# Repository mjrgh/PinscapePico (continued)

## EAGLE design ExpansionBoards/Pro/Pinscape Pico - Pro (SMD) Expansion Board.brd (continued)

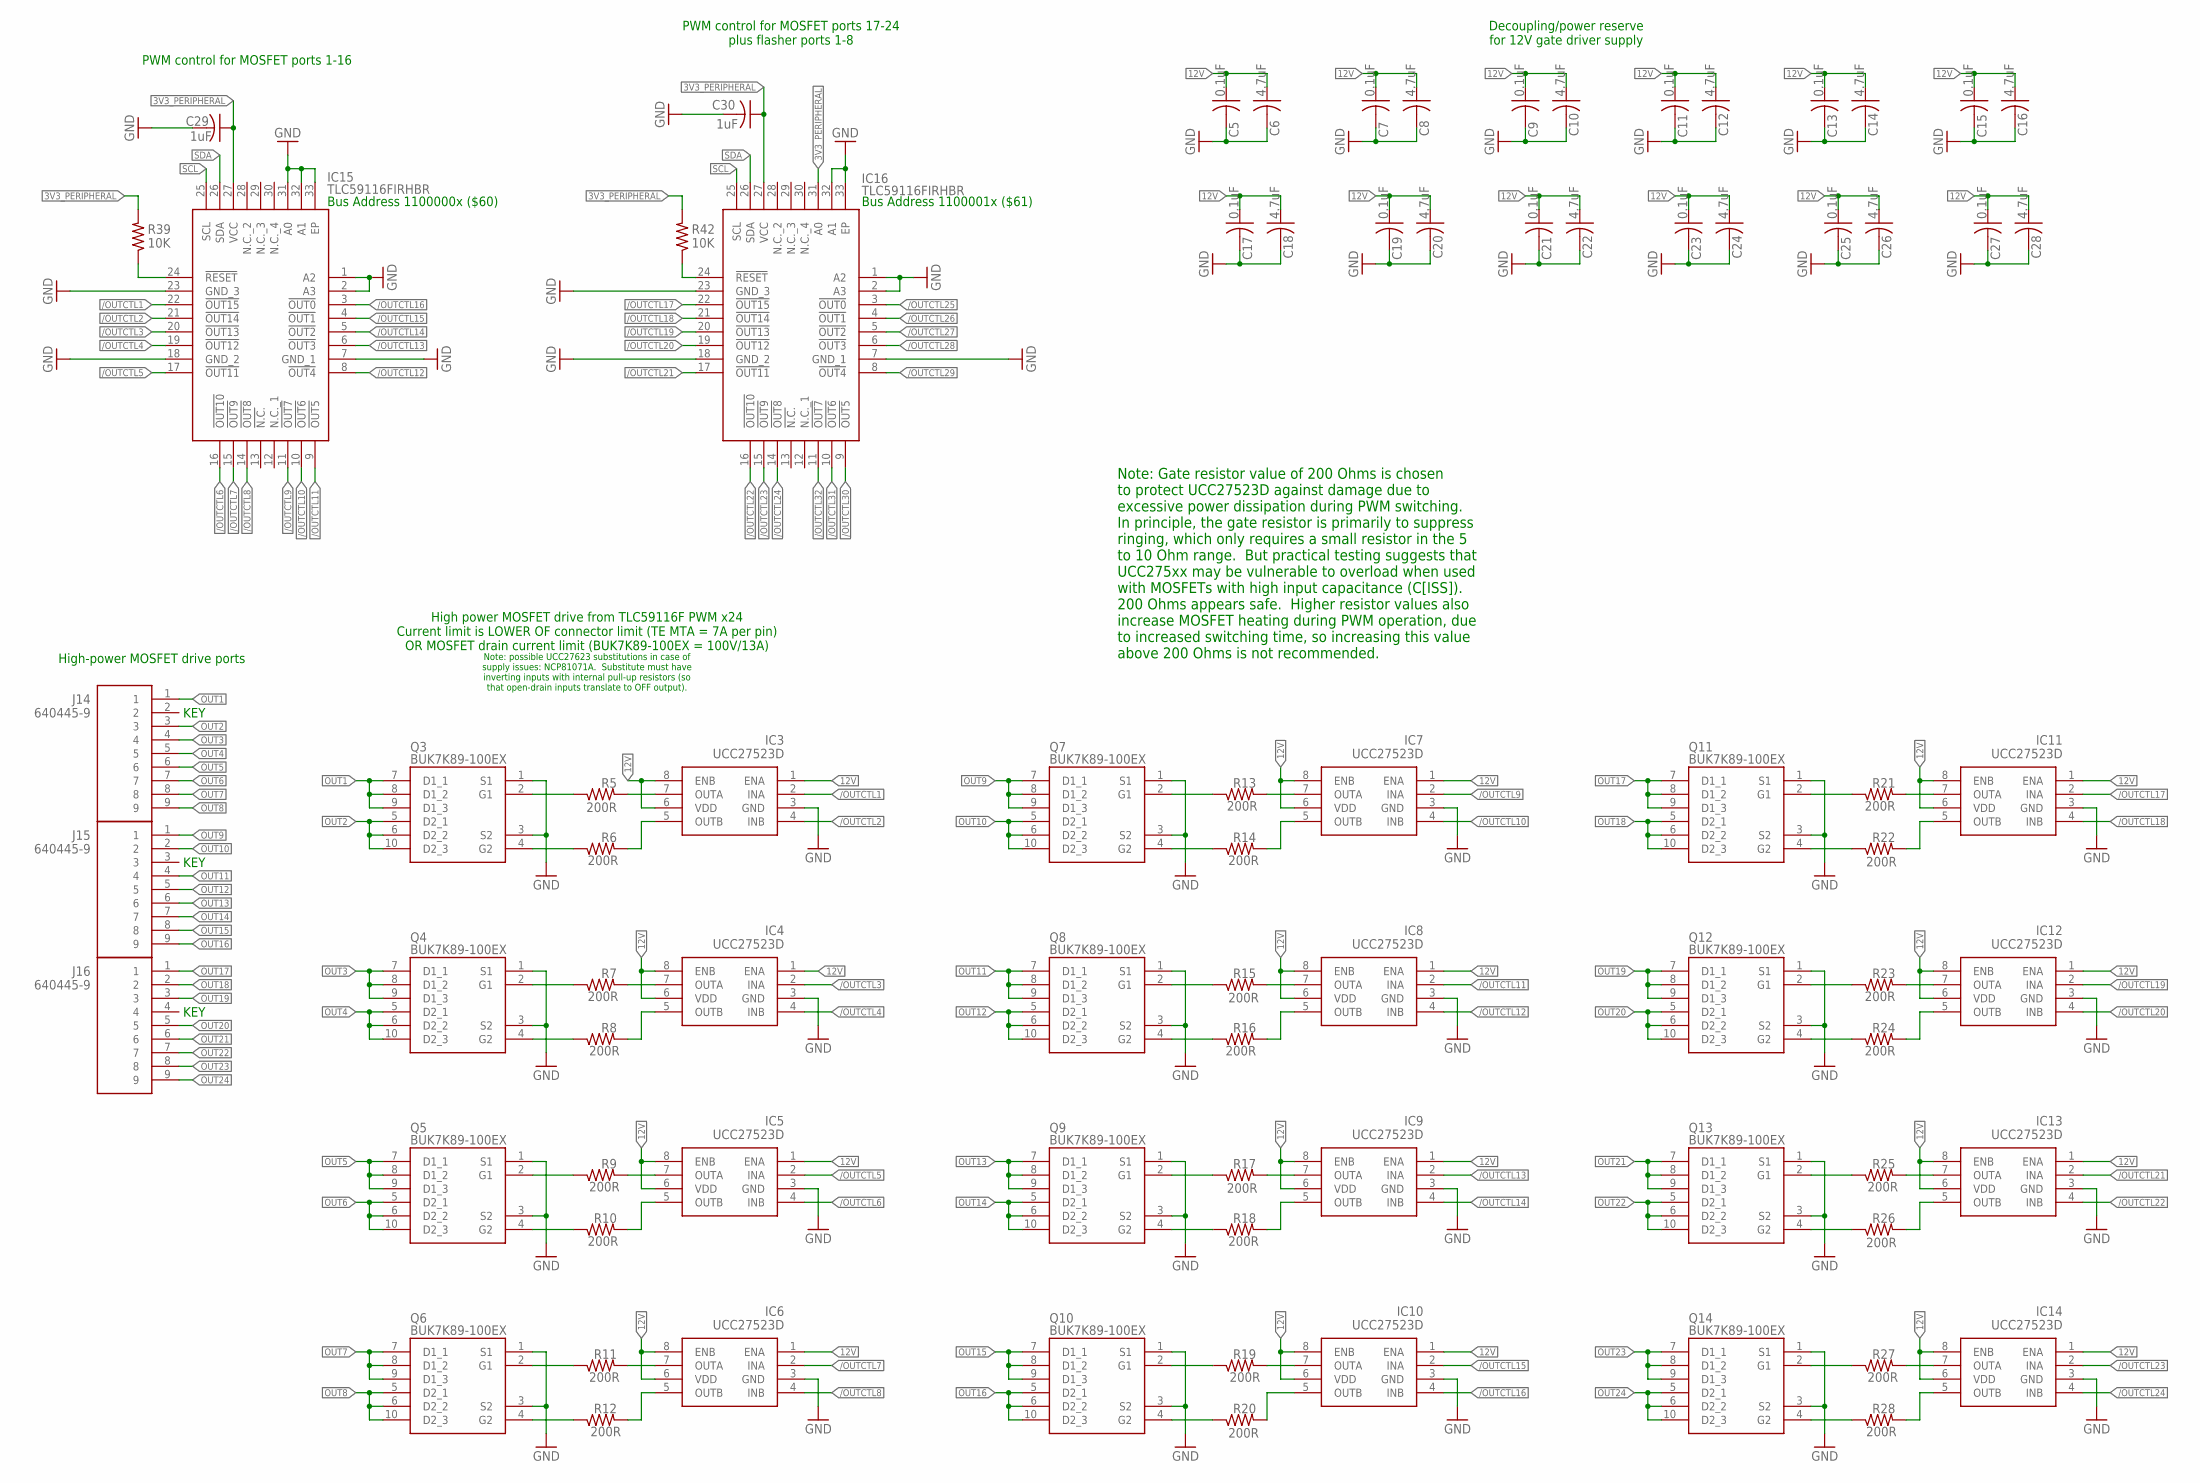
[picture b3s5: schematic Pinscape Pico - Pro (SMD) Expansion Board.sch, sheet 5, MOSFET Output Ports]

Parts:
C5, C7, C9, C11, C13, C15, C17, C19, C21, C23, C25, C27: 0.1uF; C0402
C6, C8, C10, C12, C14, C16, C18, C20, C22, C24, C26, C28: 4.7uF; C1206
C29, C30: 1uF; C0402
IC3, IC4, IC5, IC6, IC7, IC8, IC9, IC10, IC11, IC12, IC13, IC14: UCC27523D; SOIC127P600X175-8N
IC15, IC16: TLC59116FIRHBR; QFN50P500X500X100-33N
J14, J15, J16: 640445-9; SHDR9W117P0X396_1X9_3566X762X1
Q3, Q4, Q5, Q6, Q7, Q8, Q9, Q10, Q11, Q12, Q13, Q14: BUK7K89-100EX; BUK7K89100EX
R5, R6, R7, R8, R9, R10, R11, R12, R13, R14, R15, R16, R17, R18, R19, R20, R21, R22, R23, R24, R25, R26, R27, R28: 200R; R0603
R39, R42: 10K; R0402

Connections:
3V3_PERIPHERAL: C29.1, C30.1, IC15.27 (VCC), IC16.27 (VCC), IC16.31 (A0), R39.2, R42.2; also elsewhere on the board
12V: C5.1, C6.1, C7.1, C8.1, C9.1, C10.1, C11.1, C12.1, C13.1, C14.1, C15.1, C16.1, C17.1, C18.1, C19.1, C20.1, C21.1, C22.1, C23.1, C24.1, C25.1, C26.1, C27.1, C28.1, IC3.1 (ENA), IC3.6 (VDD), IC3.8 (ENB), IC4.1 (ENA), IC4.6 (VDD), IC4.8 (ENB), IC5.1 (ENA), IC5.6 (VDD), IC5.8 (ENB), IC6.1 (ENA), IC6.6 (VDD), IC6.8 (ENB), IC7.1 (ENA), IC7.6 (VDD), IC7.8 (ENB), IC8.1 (ENA), IC8.6 (VDD), IC8.8 (ENB), IC9.1 (ENA), IC9.6 (VDD), IC9.8 (ENB), IC10.1 (ENA), IC10.6 (VDD), IC10.8 (ENB), IC11.1 (ENA), IC11.6 (VDD), IC11.8 (ENB), IC12.1 (ENA), IC12.6 (VDD), IC12.8 (ENB), IC13.1 (ENA), IC13.6 (VDD), IC13.8 (ENB), IC14.1 (ENA), IC14.6 (VDD), IC14.8 (ENB); also elsewhere on the board
/OUTCTL1: IC3.2 (INA), IC15.22 (!OUT15)
/OUTCTL2: IC3.4 (INB), IC15.21 (!OUT14)
/OUTCTL3: IC4.2 (INA), IC15.20 (!OUT13)
/OUTCTL4: IC4.4 (INB), IC15.19 (!OUT12)
/OUTCTL5: IC5.2 (INA), IC15.17 (!OUT11)
/OUTCTL6: IC5.4 (INB), IC15.16 (!OUT10)
/OUTCTL7: IC6.2 (INA), IC15.15 (!OUT9)
/OUTCTL8: IC6.4 (INB), IC15.14 (!OUT8)
/OUTCTL9: IC7.2 (INA), IC15.11 (!OUT7)
/OUTCTL10: IC7.4 (INB), IC15.10 (!OUT6)
/OUTCTL11: IC8.2 (INA), IC15.9 (!OUT5)
/OUTCTL12: IC8.4 (INB), IC15.8 (!OUT4)
/OUTCTL13: IC9.2 (INA), IC15.6 (!OUT3)
/OUTCTL14: IC9.4 (INB), IC15.5 (!OUT2)
/OUTCTL15: IC10.2 (INA), IC15.4 (!OUT1)
/OUTCTL16: IC10.4 (INB), IC15.3 (!OUT0)
/OUTCTL17: IC11.2 (INA), IC16.22 (!OUT15)
/OUTCTL18: IC11.4 (INB), IC16.21 (!OUT14)
/OUTCTL19: IC12.2 (INA), IC16.20 (!OUT13)
/OUTCTL20: IC12.4 (INB), IC16.19 (!OUT12)
/OUTCTL21: IC13.2 (INA), IC16.17 (!OUT11)
/OUTCTL22: IC13.4 (INB), IC16.16 (!OUT10)
/OUTCTL23: IC14.2 (INA), IC16.15 (!OUT9)
/OUTCTL24: IC14.4 (INB), IC16.14 (!OUT8)
/OUTCTL25: IC16.3 (!OUT0); also elsewhere on the board
/OUTCTL26: IC16.4 (!OUT1); also elsewhere on the board
/OUTCTL27: IC16.5 (!OUT2); also elsewhere on the board
/OUTCTL28: IC16.6 (!OUT3); also elsewhere on the board
/OUTCTL29: IC16.8 (!OUT4); also elsewhere on the board
/OUTCTL30: IC16.9 (!OUT5); also elsewhere on the board
/OUTCTL31: IC16.10 (!OUT6); also elsewhere on the board
/OUTCTL32: IC16.11 (!OUT7); also elsewhere on the board
GND: C5.2, C6.2, C7.2, C8.2, C9.2, C10.2, C11.2, C12.2, C13.2, C14.2, C15.2, C16.2, C17.2, C18.2, C19.2, C20.2, C21.2, C22.2, C23.2, C24.2, C25.2, C26.2, C27.2, C28.2, C29.2, C30.2, IC3.3 (GND), IC4.3 (GND), IC5.3 (GND), IC6.3 (GND), IC7.3 (GND), IC8.3 (GND), IC9.3 (GND), IC10.3 (GND), IC11.3 (GND), IC12.3 (GND), IC13.3 (GND), IC14.3 (GND), IC15.1 (A2), IC15.2 (A3), IC15.7 (GND_1), IC15.18 (GND_2), IC15.23 (GND_3), IC15.31 (A0), IC15.32 (A1), IC15.33 (EP), IC16.1 (A2), IC16.2 (A3), IC16.7 (GND_1), IC16.18 (GND_2), IC16.23 (GND_3), IC16.32 (A1), IC16.33 (EP), Q3.1 (S1), Q3.3 (S2), Q4.1 (S1), Q4.3 (S2), Q5.1 (S1), Q5.3 (S2), Q6.1 (S1), Q6.3 (S2), Q7.1 (S1), Q7.3 (S2), Q8.1 (S1), Q8.3 (S2), Q9.1 (S1), Q9.3 (S2), Q10.1 (S1), Q10.3 (S2), Q11.1 (S1), Q11.3 (S2), Q12.1 (S1), Q12.3 (S2), Q13.1 (S1), Q13.3 (S2), Q14.1 (S1), Q14.3 (S2); also elsewhere on the board
unnamed: IC15.24 (!RESET), R39.1
unnamed: IC3.5 (OUTB), R6.2
unnamed: IC4.7 (OUTA), R7.2
unnamed: IC7.7 (OUTA), R13.2
unnamed: IC5.5 (OUTB), R10.2
unnamed: IC6.7 (OUTA), R11.2
unnamed: IC6.5 (OUTB), R12.2
unnamed: IC9.7 (OUTA), R17.2
unnamed: IC8.7 (OUTA), R15.2
unnamed: IC8.5 (OUTB), R16.2
unnamed: IC9.5 (OUTB), R18.2
unnamed: IC10.7 (OUTA), R19.2
unnamed: IC10.5 (OUTB), R20.2
unnamed: IC12.7 (OUTA), R23.2
unnamed: IC11.7 (OUTA), R21.2
unnamed: IC11.5 (OUTB), R22.2
unnamed: IC14.7 (OUTA), R27.2
unnamed: IC12.5 (OUTB), R24.2
unnamed: IC13.5 (OUTB), R26.2
unnamed: IC13.7 (OUTA), R25.2
unnamed: IC14.5 (OUTB), R28.2
unnamed: Q11.2 (G1), R21.1
unnamed: IC5.7 (OUTA), R9.2
unnamed: IC7.5 (OUTB), R14.2
unnamed: Q11.4 (G2), R22.1
unnamed: IC4.5 (OUTB), R8.2
unnamed: IC3.7 (OUTA), R5.2
unnamed: Q12.2 (G1), R23.1
unnamed: Q12.4 (G2), R24.1
unnamed: Q13.2 (G1), R25.1
unnamed: Q13.4 (G2), R26.1
unnamed: Q14.2 (G1), R27.1
unnamed: Q14.4 (G2), R28.1
unnamed: Q7.2 (G1), R13.1
unnamed: Q7.4 (G2), R14.1
unnamed: Q8.2 (G1), R15.1
unnamed: Q10.4 (G2), R20.1
unnamed: Q10.2 (G1), R19.1
unnamed: Q9.4 (G2), R18.1
unnamed: Q9.2 (G1), R17.1
unnamed: Q8.4 (G2), R16.1
unnamed: Q6.4 (G2), R12.1
unnamed: Q6.2 (G1), R11.1
unnamed: Q5.4 (G2), R10.1
unnamed: Q5.2 (G1), R9.1
unnamed: Q4.4 (G2), R8.1
unnamed: Q4.2 (G1), R7.1
unnamed: Q3.4 (G2), R6.1
unnamed: Q3.2 (G1), R5.1
unnamed: IC16.24 (!RESET), R42.1
OUT1: J14.1, Q3.7 (D1_1), Q3.8 (D1_2), Q3.9 (D1_3)
OUT2: J14.3, Q3.5 (D2_1), Q3.6 (D2_2), Q3.10 (D2_3)
OUT3: J14.4, Q4.7 (D1_1), Q4.8 (D1_2), Q4.9 (D1_3)
OUT4: J14.5, Q4.5 (D2_1), Q4.6 (D2_2), Q4.10 (D2_3)
OUT5: J14.6, Q5.7 (D1_1), Q5.8 (D1_2), Q5.9 (D1_3)
OUT6: J14.7, Q5.5 (D2_1), Q5.6 (D2_2), Q5.10 (D2_3)
OUT7: J14.8, Q6.7 (D1_1), Q6.8 (D1_2), Q6.9 (D1_3)
OUT8: J14.9, Q6.5 (D2_1), Q6.6 (D2_2), Q6.10 (D2_3)
OUT9: J15.1, Q7.7 (D1_1), Q7.8 (D1_2), Q7.9 (D1_3)
OUT10: J15.2, Q7.5 (D2_1), Q7.6 (D2_2), Q7.10 (D2_3)
OUT11: J15.4, Q8.7 (D1_1), Q8.8 (D1_2), Q8.9 (D1_3)
OUT12: J15.5, Q8.5 (D2_1), Q8.6 (D2_2), Q8.10 (D2_3)
OUT13: J15.6, Q9.7 (D1_1), Q9.8 (D1_2), Q9.9 (D1_3)
OUT14: J15.7, Q9.5 (D2_1), Q9.6 (D2_2), Q9.10 (D2_3)
OUT15: J15.8, Q10.7 (D1_1), Q10.8 (D1_2), Q10.9 (D1_3)
OUT16: J15.9, Q10.5 (D2_1), Q10.6 (D2_2), Q10.10 (D2_3)
OUT17: J16.1, Q11.7 (D1_1), Q11.8 (D1_2), Q11.9 (D1_3)
OUT18: J16.2, Q11.5 (D2_1), Q11.6 (D2_2), Q11.10 (D2_3)
OUT19: J16.3, Q12.7 (D1_1), Q12.8 (D1_2), Q12.9 (D1_3)
OUT20: J16.5, Q12.5 (D2_1), Q12.6 (D2_2), Q12.10 (D2_3)
OUT21: J16.6, Q13.7 (D1_1), Q13.8 (D1_2), Q13.9 (D1_3)
OUT22: J16.7, Q13.5 (D2_1), Q13.6 (D2_2), Q13.10 (D2_3)
OUT23: J16.8, Q14.7 (D1_1), Q14.8 (D1_2), Q14.9 (D1_3)
OUT24: J16.9, Q14.5 (D2_1), Q14.6 (D2_2), Q14.10 (D2_3)
SCL: IC15.25 (SCL), IC16.25 (SCL); also elsewhere on the board
SDA: IC15.26 (SDA), IC16.26 (SDA); also elsewhere on the board

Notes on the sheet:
High power MOSFET drive from TLC59116F PWM x24 Current limit is LOWER OF connector limit (TE MTA = 7A per pin) OR MOSFET drain current limit (BUK7K89-100EX = 100V/13A)
Decoupling/power reserve for 12V gate driver supply
Bus Address 1100000x ($60)
Bus Address 1100001x ($61)
PWM control for MOSFET ports 1-16
PWM control for MOSFET ports 17-24 plus flasher ports 1-8
Note: possible UCC27623 substitutions in case of supply issues: NCP81071A. Substitute must have inverting inputs with internal pull-up resistors (so that open-drain inputs translate to OFF output).
High-power MOSFET drive ports
KEY
Note: Gate resistor value of 200 Ohms is chosen to protect UCC27523D against damage due to excessive power dissipation during PWM switching. In principle, the gate resistor is primarily to suppress ringing, which only requires a small resistor in the 5 to 10 Ohm range. But practical testing suggest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

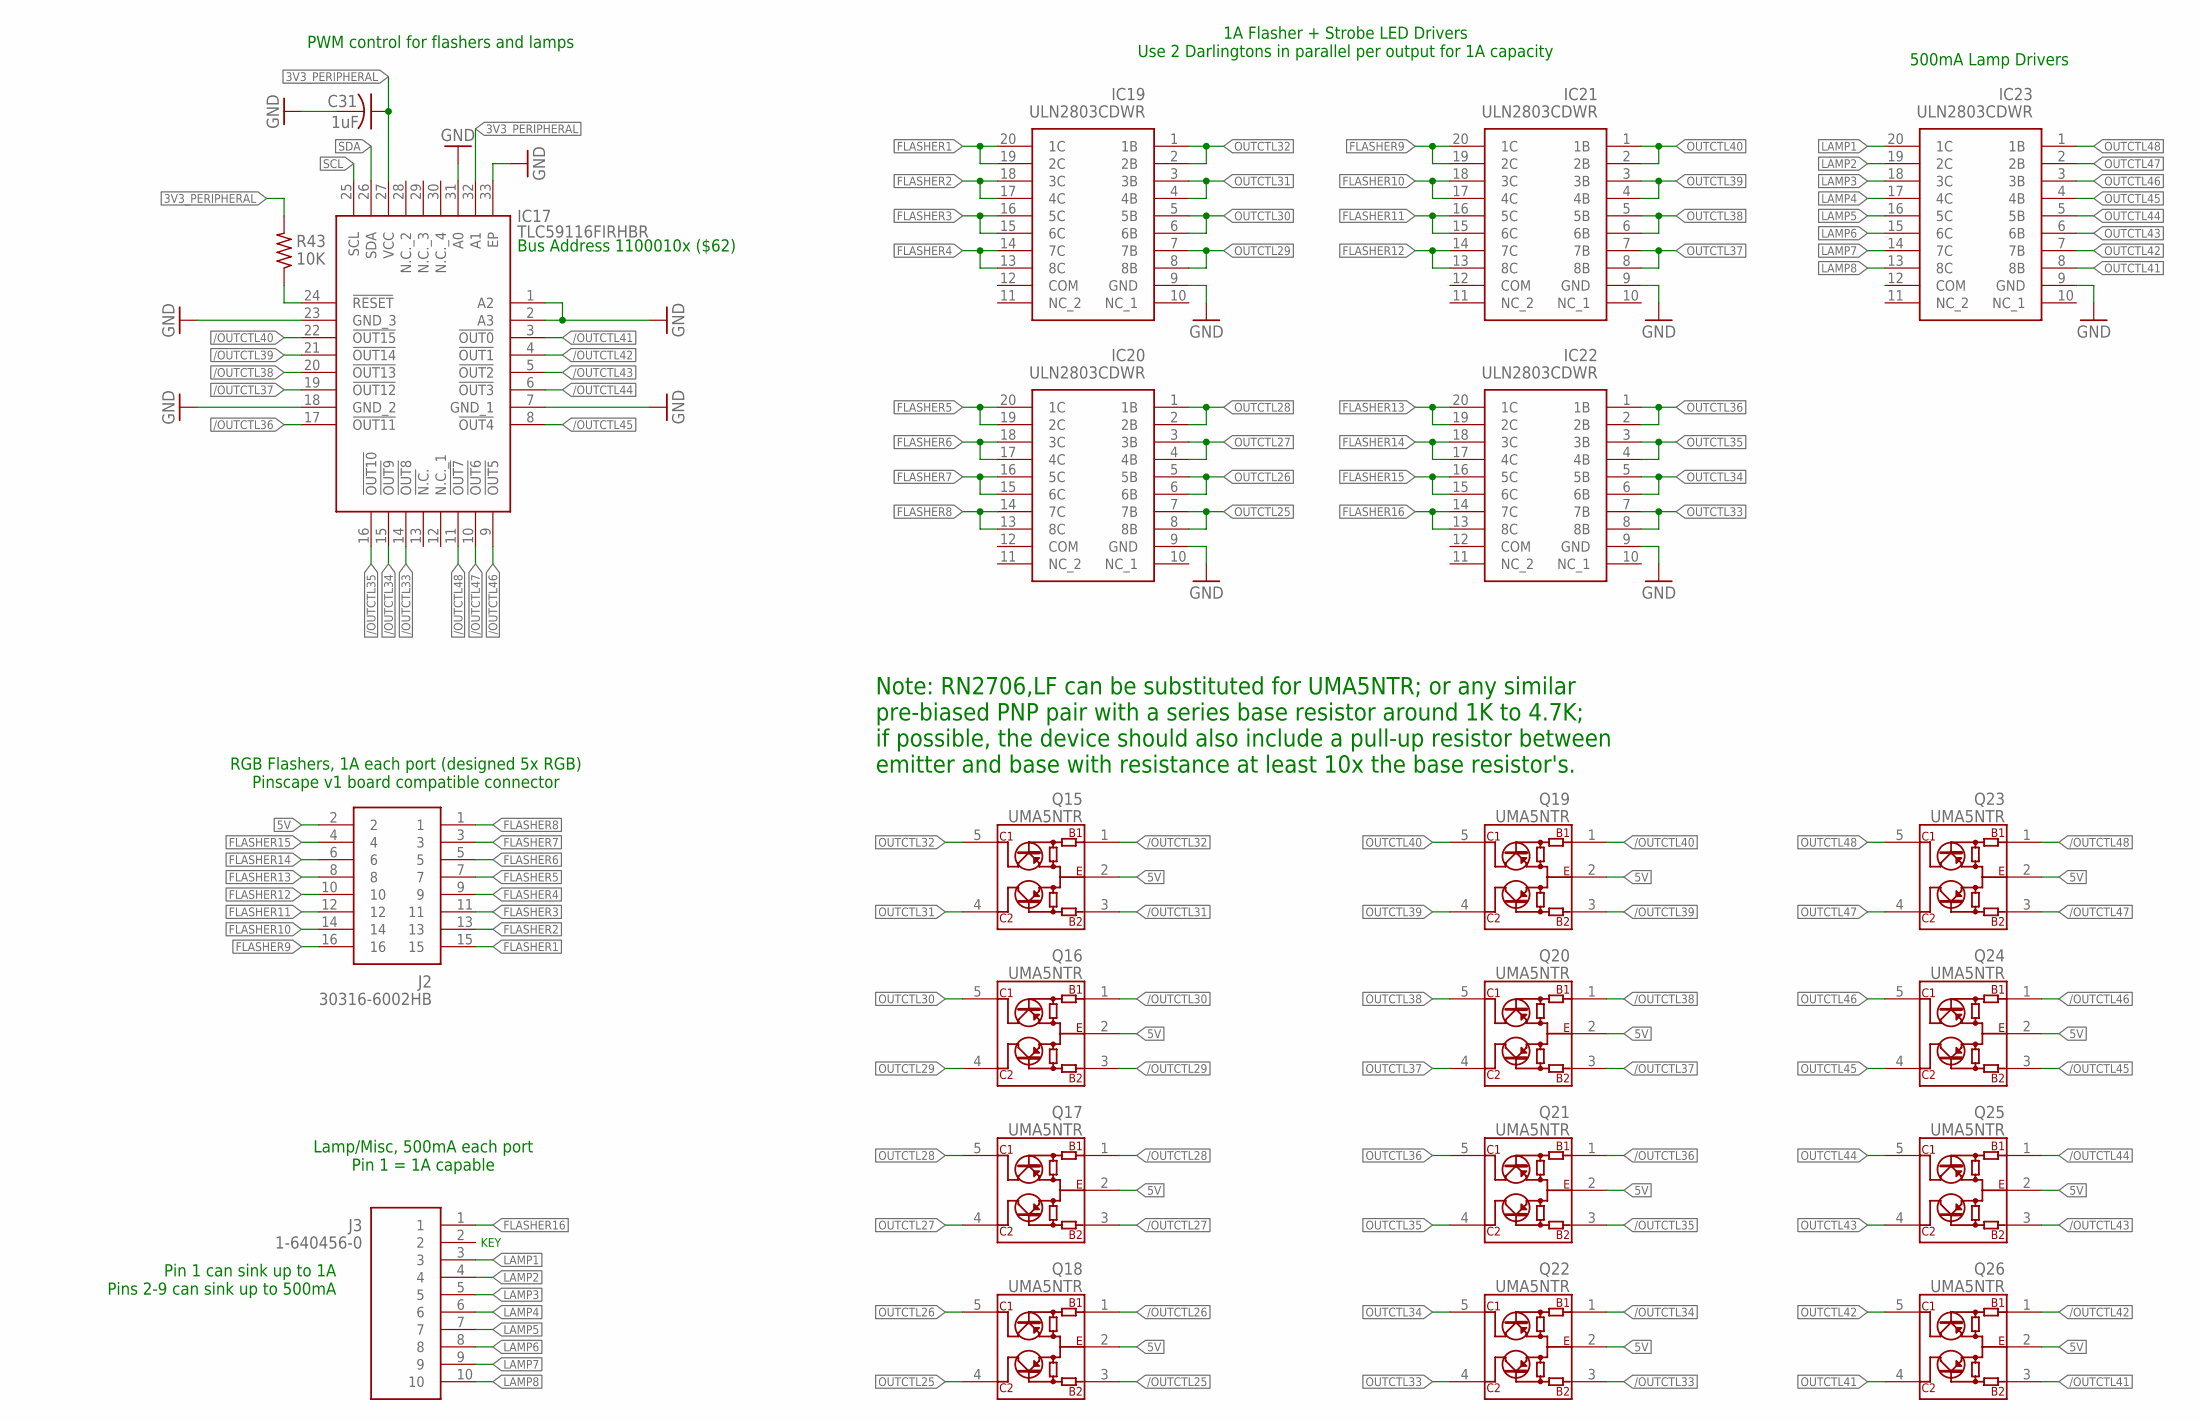
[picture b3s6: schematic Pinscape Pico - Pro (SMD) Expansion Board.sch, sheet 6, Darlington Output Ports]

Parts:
C31: 1uF; C0402
IC17: TLC59116FIRHBR; QFN50P500X500X100-33N
IC19, IC20, IC21, IC22, IC23: ULN2803CDWR; SOIC127P1030X265-20N
J2: 30316-6002HB; 3M-30316-6002HB
J3: 1-640456-0; SHDR10W66P0X254_1X10_2540X572X
Q15, Q16, Q17, Q18, Q19, Q20, Q21, Q22, Q23, Q24, Q25, Q26: UMA5NTR; SOT65P210X100-5N
R43: 10K; R0402

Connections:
3V3_PERIPHERAL: C31.1, IC17.27 (VCC), IC17.32 (A1), R43.2; also elsewhere on the board
5V: J2.2, Q15.2 (E), Q16.2 (E), Q17.2 (E), Q18.2 (E), Q19.2 (E), Q20.2 (E), Q21.2 (E), Q22.2 (E), Q23.2 (E), Q24.2 (E), Q25.2 (E), Q26.2 (E); also elsewhere on the board
/OUTCTL25: Q18.3 (B2); also elsewhere on the board
/OUTCTL26: Q18.1 (B1); also elsewhere on the board
/OUTCTL27: Q17.3 (B2); also elsewhere on the board
/OUTCTL28: Q17.1 (B1); also elsewhere on the board
/OUTCTL29: Q16.3 (B2); also elsewhere on the board
/OUTCTL30: Q16.1 (B1); also elsewhere on the board
/OUTCTL31: Q15.3 (B2); also elsewhere on the board
/OUTCTL32: Q15.1 (B1); also elsewhere on the board
/OUTCTL33: IC17.14 (!OUT8), Q22.3 (B2)
/OUTCTL34: IC17.15 (!OUT9), Q22.1 (B1)
/OUTCTL35: IC17.16 (!OUT10), Q21.3 (B2)
/OUTCTL36: IC17.17 (!OUT11), Q21.1 (B1)
/OUTCTL37: IC17.19 (!OUT12), Q20.3 (B2)
/OUTCTL38: IC17.20 (!OUT13), Q20.1 (B1)
/OUTCTL39: IC17.21 (!OUT14), Q19.3 (B2)
/OUTCTL40: IC17.22 (!OUT15), Q19.1 (B1)
/OUTCTL41: IC17.3 (!OUT0), Q26.3 (B2)
/OUTCTL42: IC17.4 (!OUT1), Q26.1 (B1)
/OUTCTL43: IC17.5 (!OUT2), Q25.3 (B2)
/OUTCTL44: IC17.6 (!OUT3), Q25.1 (B1)
/OUTCTL45: IC17.8 (!OUT4), Q24.3 (B2)
/OUTCTL46: IC17.9 (!OUT5), Q24.1 (B1)
/OUTCTL47: IC17.10 (!OUT6), Q23.3 (B2)
/OUTCTL48: IC17.11 (!OUT7), Q23.1 (B1)
FLASHER1: IC19.19 (2C), IC19.20 (1C), J2.15
FLASHER2: IC19.17 (4C), IC19.18 (3C), J2.13
FLASHER3: IC19.15 (6C), IC19.16 (5C), J2.11
FLASHER4: IC19.13 (8C), IC19.14 (7C), J2.9
FLASHER5: IC20.19 (2C), IC20.20 (1C), J2.7
FLASHER6: IC20.17 (4C), IC20.18 (3C), J2.5
FLASHER7: IC20.15 (6C), IC20.16 (5C), J2.3
FLASHER8: IC20.13 (8C), IC20.14 (7C), J2.1
FLASHER9: IC21.19 (2C), IC21.20 (1C), J2.16
FLASHER10: IC21.17 (4C), IC21.18 (3C), J2.14
FLASHER11: IC21.15 (6C), IC21.16 (5C), J2.12
FLASHER12: IC21.13 (8C), IC21.14 (7C), J2.10
FLASHER13: IC22.19 (2C), IC22.20 (1C), J2.8
FLASHER14: IC22.17 (4C), IC22.18 (3C), J2.6
FLASHER15: IC22.15 (6C), IC22.16 (5C), J2.4
FLASHER16: IC22.13 (8C), IC22.14 (7C), J3.1
GND: C31.2, IC17.1 (A2), IC17.2 (A3), IC17.7 (GND_1), IC17.18 (GND_2), IC17.23 (GND_3), IC17.31 (A0), IC17.33 (EP), IC19.9 (GND), IC20.9 (GND), IC21.9 (GND), IC22.9 (GND), IC23.9 (GND); also elsewhere on the board
LAMP1: IC23.20 (1C), J3.3
LAMP2: IC23.19 (2C), J3.4
LAMP3: IC23.18 (3C), J3.5
LAMP4: IC23.17 (4C), J3.6
LAMP5: IC23.16 (5C), J3.7
LAMP6: IC23.15 (6C), J3.8
LAMP7: IC23.14 (7C), J3.9
LAMP8: IC23.13 (8C), J3.10
unnamed: IC17.24 (!RESET), R43.1
OUTCTL25: IC20.7 (7B), IC20.8 (8B), Q18.4 (C2)
OUTCTL26: IC20.5 (5B), IC20.6 (6B), Q18.5 (C1)
OUTCTL27: IC20.3 (3B), IC20.4 (4B), Q17.4 (C2)
OUTCTL28: IC20.1 (1B), IC20.2 (2B), Q17.5 (C1)
OUTCTL29: IC19.7 (7B), IC19.8 (8B), Q16.4 (C2)
OUTCTL30: IC19.5 (5B), IC19.6 (6B), Q16.5 (C1)
OUTCTL31: IC19.3 (3B), IC19.4 (4B), Q15.4 (C2)
OUTCTL32: IC19.1 (1B), IC19.2 (2B), Q15.5 (C1)
OUTCTL33: IC22.7 (7B), IC22.8 (8B), Q22.4 (C2)
OUTCTL34: IC22.5 (5B), IC22.6 (6B), Q22.5 (C1)
OUTCTL35: IC22.3 (3B), IC22.4 (4B), Q21.4 (C2)
OUTCTL36: IC22.1 (1B), IC22.2 (2B), Q21.5 (C1)
OUTCTL37: IC21.7 (7B), IC21.8 (8B), Q20.4 (C2)
OUTCTL38: IC21.5 (5B), IC21.6 (6B), Q20.5 (C1)
OUTCTL39: IC21.3 (3B), IC21.4 (4B), Q19.4 (C2)
OUTCTL40: IC21.1 (1B), IC21.2 (2B), Q19.5 (C1)
OUTCTL41: IC23.8 (8B), Q26.4 (C2)
OUTCTL42: IC23.7 (7B), Q26.5 (C1)
OUTCTL43: IC23.6 (6B), Q25.4 (C2)
OUTCTL44: IC23.5 (5B), Q25.5 (C1)
OUTCTL45: IC23.4 (4B), Q24.4 (C2)
OUTCTL46: IC23.3 (3B), Q24.5 (C1)
OUTCTL47: IC23.2 (2B), Q23.4 (C2)
OUTCTL48: IC23.1 (1B), Q23.5 (C1)
SCL: IC17.25 (SCL); also elsewhere on the board
SDA: IC17.26 (SDA); also elsewhere on the board

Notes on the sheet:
1A Flasher + Strobe LED Drivers Use 2 Darlingtons in parallel per output for 1A capacity
500mA Lamp Drivers
RGB Flashers, 1A each port (designed 5x RGB) Pinscape v1 board compatible connector
Lamp/Misc, 500mA each port Pin 1 = 1A capable
Pin 1 can sink up to 1A Pins 2-9 can sink up to 500mA
Bus Address 1100010x ($62)
Note: RN2706,LF can be substituted for UMA5NTR; or any similar pre-biased PNP pair with a series base resistor around 1K to 4.7K; if possible, the device should also include a pull-up resistor between emitter and base with resistance at least 10x the base resistor's.
PWM control for flashers and lamps
KEY

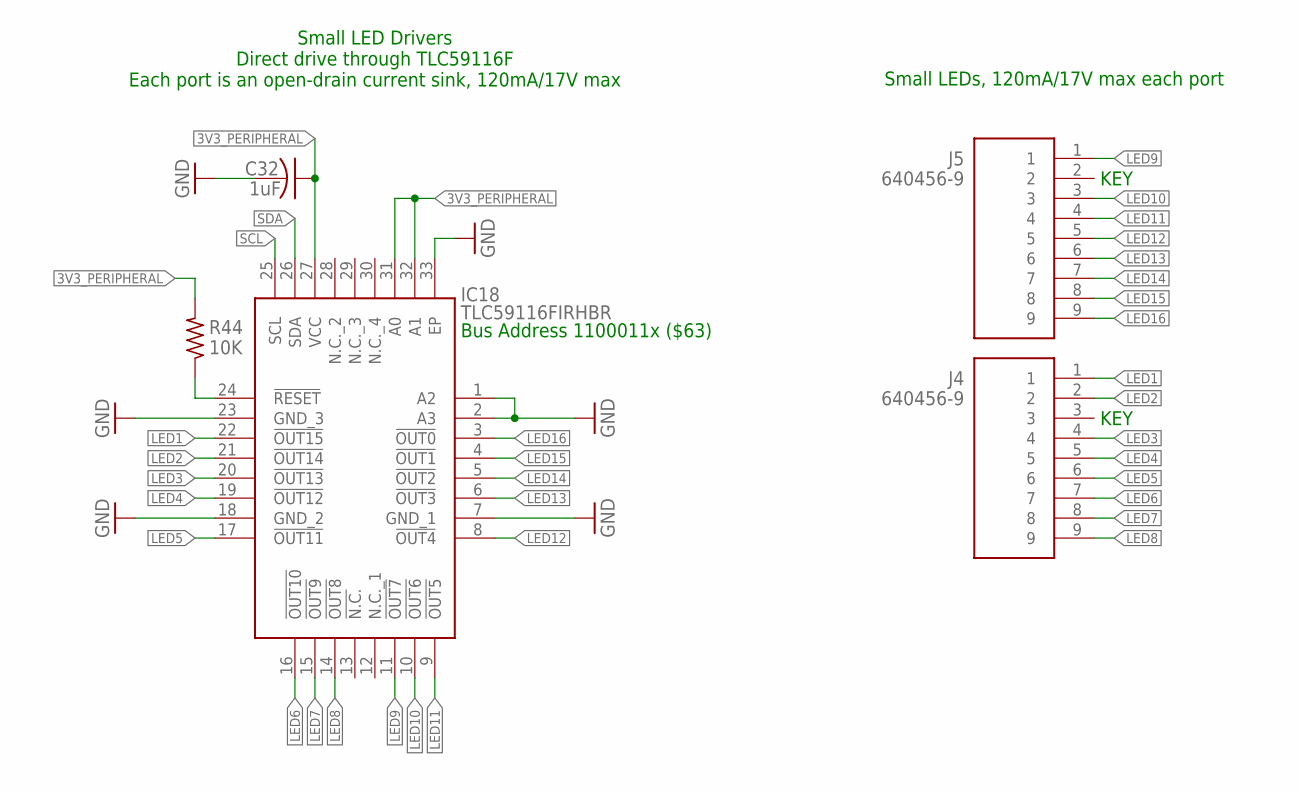
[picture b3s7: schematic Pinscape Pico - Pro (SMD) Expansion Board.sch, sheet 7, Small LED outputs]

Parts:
C32: 1uF; C0402
IC18: TLC59116FIRHBR; QFN50P500X500X100-33N
J4, J5: 640456-9; SHDR9W66P0X254_1X9_2286X572X10
R44: 10K; R0402

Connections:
3V3_PERIPHERAL: C32.1, IC18.27 (VCC), IC18.31 (A0), IC18.32 (A1), R44.2; also elsewhere on the board
GND: C32.2, IC18.1 (A2), IC18.2 (A3), IC18.7 (GND_1), IC18.18 (GND_2), IC18.23 (GND_3), IC18.33 (EP); also elsewhere on the board
LED1: IC18.22 (!OUT15), J4.1
LED2: IC18.21 (!OUT14), J4.2
LED3: IC18.20 (!OUT13), J4.4
LED4: IC18.19 (!OUT12), J4.5
LED5: IC18.17 (!OUT11), J4.6
LED6: IC18.16 (!OUT10), J4.7
LED7: IC18.15 (!OUT9), J4.8
LED8: IC18.14 (!OUT8), J4.9
LED9: IC18.11 (!OUT7), J5.1
LED10: IC18.10 (!OUT6), J5.3
LED11: IC18.9 (!OUT5), J5.4
LED12: IC18.8 (!OUT4), J5.5
LED13: IC18.6 (!OUT3), J5.6
LED14: IC18.5 (!OUT2), J5.7
LED15: IC18.4 (!OUT1), J5.8
LED16: IC18.3 (!OUT0), J5.9
unnamed: IC18.24 (!RESET), R44.1
SCL: IC18.25 (SCL); also elsewhere on the board
SDA: IC18.26 (SDA); also elsewhere on the board

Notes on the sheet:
Small LEDs, 120mA/17V max each port
Small LED Drivers Direct drive through TLC59116F Each port is an open-drain current sink, 120mA/17V max
Bus Address 1100011x ($63)
KEY

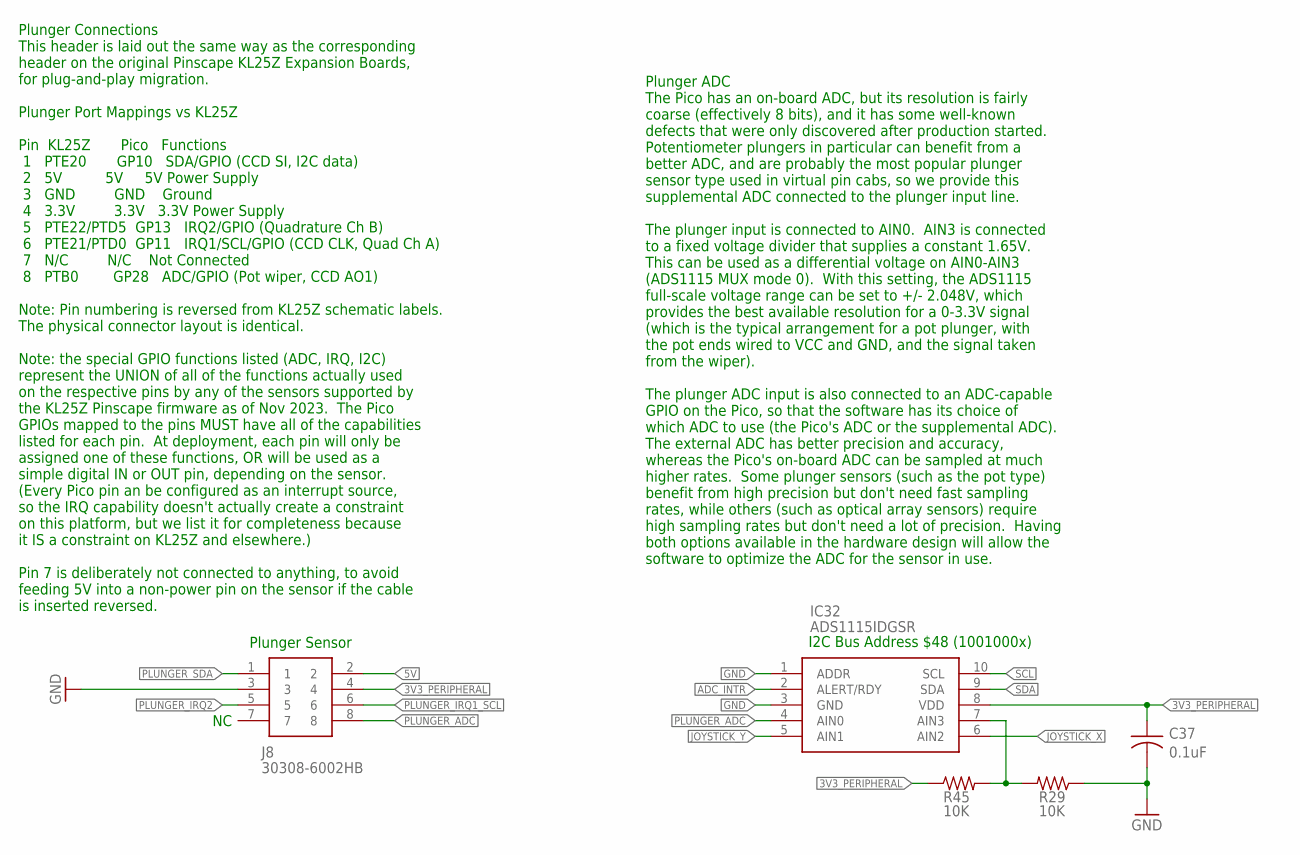
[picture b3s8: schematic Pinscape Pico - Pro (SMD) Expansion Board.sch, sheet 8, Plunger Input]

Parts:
C37: 0.1uF; C0402
IC32: ADS1115IDGSR; SOP50P490X110-10N
J8: 30308-6002HB; SHDR8W69P254_2X4_1780X878X955P
R29, R45: 10K; R0603

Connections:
3V3_PERIPHERAL: C37.1, IC32.8 (VDD), J8.4, R45.1; also elsewhere on the board
5V: J8.2; also elsewhere on the board
ADC_INTR: IC32.2 (ALERT/RDY); also elsewhere on the board
GND: C37.2, IC32.1 (ADDR), IC32.3 (GND), J8.3, R29.1; also elsewhere on the board
JOYSTICK_X: IC32.6 (AIN2); also elsewhere on the board
JOYSTICK_Y: IC32.5 (AIN1); also elsewhere on the board
unnamed: IC32.7 (AIN3), R29.2, R45.2
PLUNGER_ADC: IC32.4 (AIN0), J8.8; also elsewhere on the board
PLUNGER_IRQ1_SCL: J8.6; also elsewhere on the board
PLUNGER_IRQ2: J8.5; also elsewhere on the board
PLUNGER_SDA: J8.1; also elsewhere on the board
SCL: IC32.10 (SCL); also elsewhere on the board
SDA: IC32.9 (SDA); also elsewhere on the board

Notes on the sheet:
Plunger Sensor
Plunger Connections This header is laid out the same way as the corresponding header on the original Pinscape KL25Z Expansion Boards, for plug-and-play migration. Plunger Port Mappings vs KL25Z Pin KL25Z Pico Functions 1 PTE20 GP10 SDA/GPIO (CCD SI, I2C data) 2 5V 5V 5V Power Supply 3 GND GND Groun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
Plunger ADC The Pico has an on-board ADC, but its resolution is fairly coarse (effectively 8 bits), and it has some well-known defects that were only discovered after production started. Potentiometer plungers in particular can benefit from a better ADC, and are probably the most popular plunger se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
I2C Bus Address $48 (1001000x)

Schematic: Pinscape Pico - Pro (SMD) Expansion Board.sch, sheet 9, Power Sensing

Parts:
C36: 0.1uF; C0402
IC29: SN74LVC1G175DCKR; SOP65P210X110-6N
IC30: APX809S-29SA-7; SOT23_DIO; MANUFACTURER_PART_NUMBER APX809S-40SA-7
IC31: LTV-827S; SOP254P1016X460-8N
R32, R33: 10K; R0402; PARTNO 660-MS1/4DCT52R1002
R34: 360R; R0402; PARTNO 660-MS1/4DCT52R1002
R35: 240R; R0402; PARTNO 594-SFR16S0005600FR5

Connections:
3V3_PERIPHERAL: IC31.6 (C_1); also elsewhere on the board
5V: C36.1, IC29.3 (D), IC29.5 (VCC), IC30.3 (VCC), IC31.8 (C_2); also elsewhere on the board
GND: C36.2, IC29.2 (GND), IC30.1 (GND), R32.1, R33.1, R34.2, R35.2; also elsewhere on the board
unnamed: IC29.1 (CLK), IC31.7 (E_2), R32.2
unnamed: IC31.2 (K_1), R35.1
unnamed: IC29.6 (!CLR), IC30.2 (!RESET)
unnamed: IC31.4 (K_2), R34.1
unnamed: IC29.4 (Q), IC31.3 (A_2)
PSU2_STATUS_SENSE: IC31.5 (E_1), R33.2; also elsewhere on the board
PSU2_STATUS_SET: IC31.1 (A_1); also elsewhere on the board

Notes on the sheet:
PSU2 Power Sensing This circuit monitors the status of a secondary power supply (PSU2) that's hard-switched on and off with the overall pinball cabinet power. The status circuit maintains its own memory of the power state, independently of the Pico's power state, which satisfies two important condi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
POR part selection: The POR is triggered by the voltage on the 5V supply crossing a threshold voltage, so we must choose a POR whose threshold voltage slightly below the MINIMUM voltage that the 5V supply maintains when powered on and operating stably. Nominally, this would be 4.75V for an ATX supp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
Note: RESET signal must be ACTIVE LOW

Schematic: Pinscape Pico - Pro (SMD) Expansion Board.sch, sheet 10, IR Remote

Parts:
D1, D2: 1N4148WT-7; 1N4148WT7
J6: 640454-2; HDRV2W66P0X254_1X2_762X572X100
J7: 215079-4; 2150794
Q27: DSS8110Y-7; SOT65P210X110-6N
R30: 540R; R0402
R31: 2R5; R0603

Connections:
3V3_PERIPHERAL: J7.1; also elsewhere on the board
5V: J6.1; also elsewhere on the board
GND: D2.1 (K), J7.2, J7.4, R31.1; also elsewhere on the board
IR_IN: J7.3; also elsewhere on the board
IR_LED_CATHODE: J6.2, Q27.1 (C_1), Q27.2 (C_2), Q27.5 (C_3), Q27.6 (C_4)
IR_OUT: R30.2; also elsewhere on the board
unnamed: Q27.4 (E), R31.2
unnamed: D1.2 (A), Q27.3 (B), R30.1
unnamed: D1.1 (K), D2.2 (A)

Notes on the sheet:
IR REMOTE RECEIVER CONNECTOR This header allows connecting an IR receiver (TSOP38438) on a separate circuit board, connected to the main board with a 4-conductor ribbon cable. (Ribbon cable was chosen for the sake of signal integrity.) The reason for placing the receiver off-board is so that it can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
===> IRED Cathode (-)
===> IRED Anode (+)
Note: TE Connectivity Micro-Match 215079-4 base pairs with 215083-4 on-cable IDC connector.
CURRENT-SENSE RESISTOR Resistor sets current to I(LED) = 0.5V/R R=2.5 ohms -> 200mA current
IR REMOTE CONTROL TRANSMITTER Use with TSAL6400 IRED or equivalent, with a peak wavelength around 940nm. Set the current-sense resistor according to the desired forward current on the IR LED. No external current-limiting resistor is needed. Two IR LEDs can be connected in series provided that Vf is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

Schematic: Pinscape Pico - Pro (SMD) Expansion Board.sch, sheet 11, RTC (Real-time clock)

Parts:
BATT1: BH-123A-1
C40, C41: 100nF; C0402
IC34: RV-3032-C7; RV3032C7
R46: 10K; R0402
R49: 100R; R0402

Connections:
3V3_PERIPHERAL: C40.1, IC34.6 (VDD); also elsewhere on the board
GND: BATT1.-, C40.2, C41.2, IC34.5 (VSS), R46.1; also elsewhere on the board
unnamed: BATT1.+, R49.2
unnamed: IC34.4 (EVI), R46.2
unnamed: C41.1, IC34.1 (VBACKUP), R49.1
SCL: IC34.8 (SCL); also elsewhere on the board
SDA: IC34.2 (SDA); also elsewhere on the board

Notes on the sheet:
3V CR2032
I2C Addr 1101000x (68)
Real-Time Clock/Calendar with battery backup (optional)
These parts provide timekeeping for the Pico across CPU resets, and with the backup battery installed, keeps time even when the main USB power is off or the board is disconnected from the host. These parts are optional; if the RTC feature isn't needed, simply leave the RTC chip and battery holder u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

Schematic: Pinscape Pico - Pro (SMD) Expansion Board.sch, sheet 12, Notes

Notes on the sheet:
I2C Addresses Use 7-bit address notation, per Pico SDK conventions $18 LIS3DHTR (accelerometer) $48 IC29 ADS1115 (ADC) $51 IC32 RV-3032-C7 (RTC) $60 IC15 TLC59116F (PWM) $61 IC16 TLC59116F (PWM) $62 IC17 TLC59116F (PWM) $63 IC18 TLC59116F (PWM) Note: TLC59116F addresses $68 and $6B are reserved; do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
Reserved Pico PWM Channels Note: PWM channels associated with the pins assigned to the plunger sensor interface are marked as reserved because some sensors require one or more PWM inputs (e.g., for clock signals). Whether or not these channels are actually used as PWM in a deployment depends on whi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
General Notes: 1. Avoid routing signals under the I2C (SDA/SCL) traces. When unavoidable, route underlying signal traces at right angles to the I2C traces to minimize coupling.
Copyright and License Info Pinscape Pico "Pro" Expansion Board Copyright 2024, 2025 Michael J Roberts BSD 3-clause license

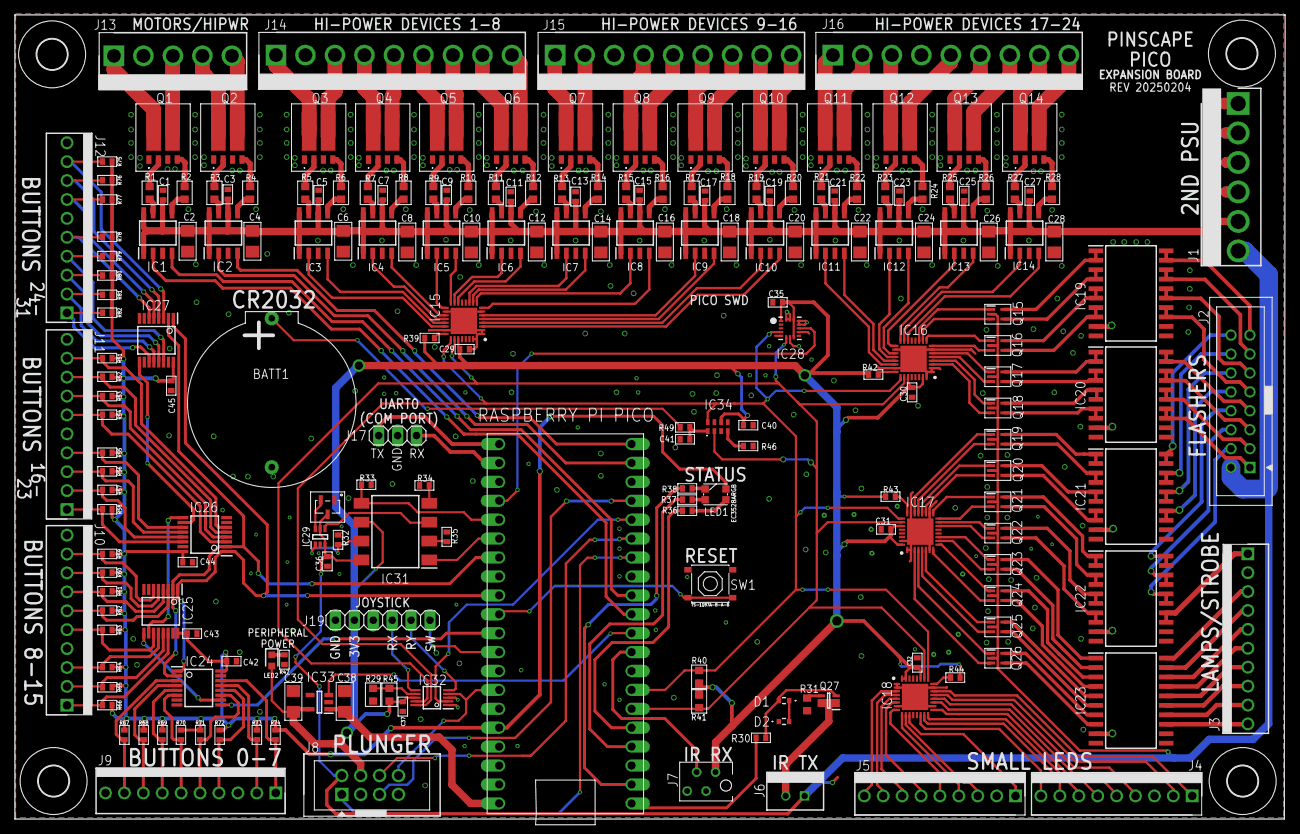
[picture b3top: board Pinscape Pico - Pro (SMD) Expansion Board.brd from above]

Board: 2 copper layers, 170.6 x 108.0 mm, 213 parts (0 on the bottom side), 287 nets.

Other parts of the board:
U$1, U$2, U$3, U$4: 4,1
